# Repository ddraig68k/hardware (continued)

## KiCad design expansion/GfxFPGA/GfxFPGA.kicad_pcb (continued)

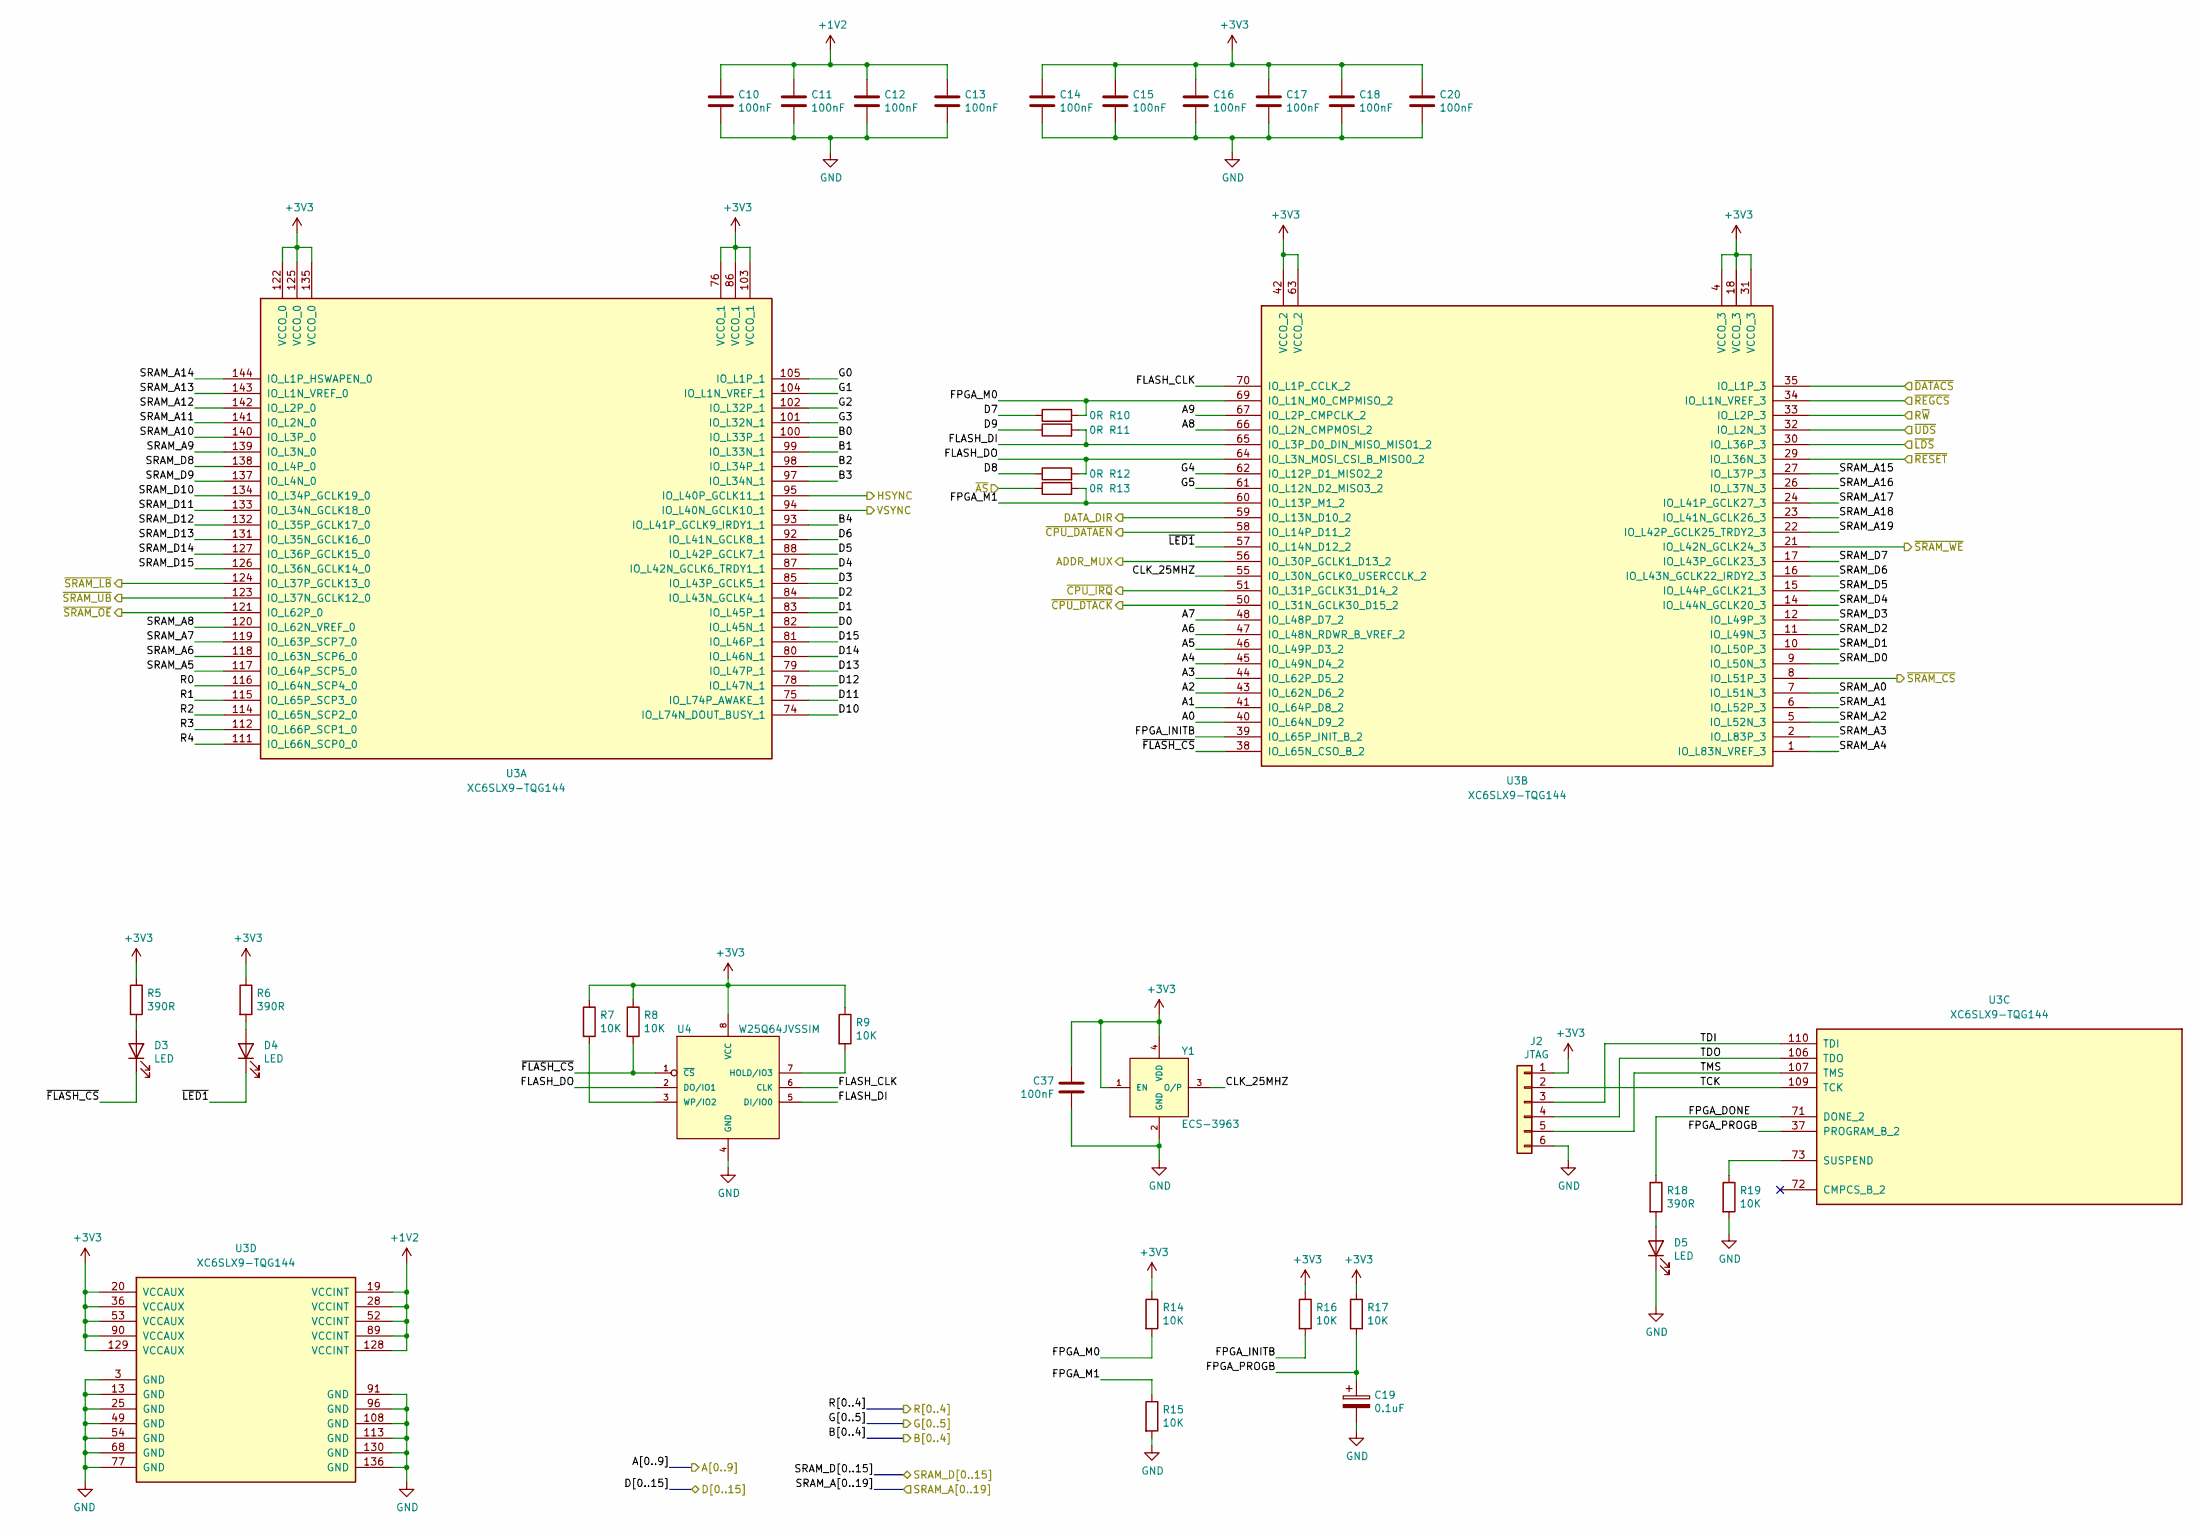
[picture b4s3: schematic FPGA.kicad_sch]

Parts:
C10, C11, C12, C13, C14, C15, C16, C17, C18, C20, C37: 100nF; C_0805_2012Metric
C19: 0.1uF; CP_Elec_4x5.3
D3, D4, D5: LED; LED_1206_3216Metric
J2: JTAG; PinHeader_1x06_P2.54mm_Vertical
R5, R6, R18: 390R; R_0805_2012Metric
R7, R8, R9, R14, R15, R16, R17, R19: 10K; R_0805_2012Metric
R10, R11, R12, R13: 0R; R_0805_2012Metric
U3: XC6SLX9-TQG144; TQ144
U4: W25Q64JVSSIM; SOIC127P790X195-8N
Y1: ECS-3963; OSC_ECS-3963; PARTREV N/A

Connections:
+1V2: C10.1, C11.1, C12.1, C13.1, U3.19 (VCCINT), U3.28 (VCCINT), U3.52 (VCCINT), U3.89 (VCCINT), U3.128 (VCCINT); also elsewhere on the board
+3V3: C14.1, C15.1, C16.1, C17.1, C18.1, C20.1, C37.1, J2.1, R5.1, R6.1, R7.1, R8.1, R9.1, R14.1, R16.1, R17.1, U3.4 (VCCO_3), U3.18 (VCCO_3), U3.20 (VCCAUX), U3.31 (VCCO_3), U3.36 (VCCAUX), U3.42 (VCCO_2), U3.53 (VCCAUX), U3.63 (VCCO_2), U3.76 (VCCO_1), U3.86 (VCCO_1), U3.90 (VCCAUX), U3.103 (VCCO_1), U3.122 (VCCO_0), U3.125 (VCCO_0), U3.129 (VCCAUX), U3.135 (VCCO_0), U4.8 (VCC), Y1.1 (EN), Y1.4 (VDD); also elsewhere on the board
/FPGA/A0: U3.40 (IO_L64N_D9_2); also elsewhere on the board
/FPGA/A1: U3.41 (IO_L64P_D8_2); also elsewhere on the board
/FPGA/A2: U3.43 (IO_L62N_D6_2); also elsewhere on the board
/FPGA/A3: U3.44 (IO_L62P_D5_2); also elsewhere on the board
/FPGA/A4: U3.45 (IO_L49N_D4_2); also elsewhere on the board
/FPGA/A5: U3.46 (IO_L49P_D3_2); also elsewhere on the board
/FPGA/A6: U3.47 (IO_L48N_RDWR_B_VREF_2); also elsewhere on the board
/FPGA/A7: U3.48 (IO_L48P_D7_2); also elsewhere on the board
/FPGA/A8: U3.66 (IO_L2N_CMPMOSI_2); also elsewhere on the board
/FPGA/A9: U3.67 (IO_L2P_CMPCLK_2); also elsewhere on the board
/FPGA/ADDR_MUX: U3.56 (IO_L30P_GCLK1_D13_2); also elsewhere on the board
/FPGA/B0: U3.100 (IO_L33P_1); also elsewhere on the board
/FPGA/B1: U3.99 (IO_L33N_1); also elsewhere on the board
/FPGA/B2: U3.98 (IO_L34P_1); also elsewhere on the board
/FPGA/B3: U3.97 (IO_L34N_1); also elsewhere on the board
/FPGA/B4: U3.93 (IO_L41P_GCLK9_IRDY1_1); also elsewhere on the board
/FPGA/CLK_25MHZ: U3.55 (IO_L30N_GCLK0_USERCCLK_2), Y1.3 (O/P)
/FPGA/D0: U3.82 (IO_L45N_1); also elsewhere on the board
/FPGA/D1: U3.83 (IO_L45P_1); also elsewhere on the board
/FPGA/D2: U3.84 (IO_L43N_GCLK4_1); also elsewhere on the board
/FPGA/D3: U3.85 (IO_L43P_GCLK5_1); also elsewhere on the board
/FPGA/D4: U3.87 (IO_L42N_GCLK6_TRDY1_1); also elsewhere on the board
/FPGA/D5: U3.88 (IO_L42P_GCLK7_1); also elsewhere on the board
/FPGA/D6: U3.92 (IO_L41N_GCLK8_1); also elsewhere on the board
/FPGA/D7: R10.1; also elsewhere on the board
/FPGA/D8: R12.1; also elsewhere on the board
/FPGA/D9: R11.1; also elsewhere on the board
/FPGA/D10: U3.74 (IO_L74N_DOUT_BUSY_1); also elsewhere on the board
/FPGA/D11: U3.75 (IO_L74P_AWAKE_1); also elsewhere on the board
/FPGA/D12: U3.78 (IO_L47N_1); also elsewhere on the board
/FPGA/D13: U3.79 (IO_L47P_1); also elsewhere on the board
/FPGA/D14: U3.80 (IO_L46N_1); also elsewhere on the board
/FPGA/D15: U3.81 (IO_L46P_1); also elsewhere on the board
/FPGA/DATA_DIR: U3.59 (IO_L13N_D10_2); also elsewhere on the board
/FPGA/FLASH_CLK: U3.70 (IO_L1P_CCLK_2), U4.6 (CLK)
/FPGA/FLASH_DI: R11.2, U3.65 (IO_L3P_D0_DIN_MISO_MISO1_2), U4.5 (DI/IO0)
/FPGA/FLASH_DO: R12.2, U3.64 (IO_L3N_MOSI_CSI_B_MISO0_2), U4.2 (DO/IO1)
/FPGA/FPGA_DONE: R18.1, U3.71 (DONE_2)
/FPGA/FPGA_INITB: R16.2, U3.39 (IO_L65P_INIT_B_2)
/FPGA/FPGA_M0: R10.2, R14.2, U3.69 (IO_L1N_M0_CMPMISO_2)
/FPGA/FPGA_M1: R13.2, R15.1, U3.60 (IO_L13P_M1_2)
/FPGA/FPGA_PROGB: C19.1, R17.2, U3.37 (PROGRAM_B_2)
/FPGA/G0: U3.105 (IO_L1P_1); also elsewhere on the board
/FPGA/G1: U3.104 (IO_L1N_VREF_1); also elsewhere on the board
/FPGA/G2: U3.102 (IO_L32P_1); also elsewhere on the board
/FPGA/G3: U3.101 (IO_L32N_1); also elsewhere on the board
/FPGA/G4: U3.62 (IO_L12P_D1_MISO2_2); also elsewhere on the board
/FPGA/G5: U3.61 (IO_L12N_D2_MISO3_2); also elsewhere on the board
/FPGA/HSYNC: U3.95 (IO_L40P_GCLK11_1); also elsewhere on the board
/FPGA/R0: U3.116 (IO_L64N_SCP4_0); also elsewhere on the board
/FPGA/R1: U3.115 (IO_L65P_SCP3_0); also elsewhere on the board
/FPGA/R2: U3.114 (IO_L65N_SCP2_0); also elsewhere on the board
/FPGA/R3: U3.112 (IO_L66P_SCP1_0); also elsewhere on the board
/FPGA/R4: U3.111 (IO_L66N_SCP0_0); also elsewhere on the board
/FPGA/R~W: U3.33 (IO_L2P_3); also elsewhere on the board
/FPGA/SRAM_A0: U3.7 (IO_L51N_3); also elsewhere on the board
/FPGA/SRAM_A1: U3.6 (IO_L52P_3); also elsewhere on the board
/FPGA/SRAM_A2: U3.5 (IO_L52N_3); also elsewhere on the board
/FPGA/SRAM_A3: U3.2 (IO_L83P_3); also elsewhere on the board
/FPGA/SRAM_A4: U3.1 (IO_L83N_VREF_3); also elsewhere on the board
/FPGA/SRAM_A5: U3.117 (IO_L64P_SCP5_0); also elsewhere on the board
/FPGA/SRAM_A6: U3.118 (IO_L63N_SCP6_0); also elsewhere on the board
/FPGA/SRAM_A7: U3.119 (IO_L63P_SCP7_0); also elsewhere on the board
/FPGA/SRAM_A8: U3.120 (IO_L62N_VREF_0); also elsewhere on the board
/FPGA/SRAM_A9: U3.139 (IO_L3N_0); also elsewhere on the board
/FPGA/SRAM_A10: U3.140 (IO_L3P_0); also elsewhere on the board
/FPGA/SRAM_A11: U3.141 (IO_L2N_0); also elsewhere on the board
/FPGA/SRAM_A12: U3.142 (IO_L2P_0); also elsewhere on the board
/FPGA/SRAM_A13: U3.143 (IO_L1N_VREF_0); also elsewhere on the board
/FPGA/SRAM_A14: U3.144 (IO_L1P_HSWAPEN_0); also elsewhere on the board
/FPGA/SRAM_A15: U3.27 (IO_L37P_3); also elsewhere on the board
/FPGA/SRAM_A16: U3.26 (IO_L37N_3); also elsewhere on the board
/FPGA/SRAM_A17: U3.24 (IO_L41P_GCLK27_3); also elsewhere on the board
/FPGA/SRAM_A18: U3.23 (IO_L41N_GCLK26_3); also elsewhere on the board
/FPGA/SRAM_A19: U3.22 (IO_L42P_GCLK25_TRDY2_3); also elsewhere on the board
/FPGA/SRAM_D0: U3.9 (IO_L50N_3); also elsewhere on the board
/FPGA/SRAM_D1: U3.10 (IO_L50P_3); also elsewhere on the board
/FPGA/SRAM_D2: U3.11 (IO_L49N_3); also elsewhere on the board
/FPGA/SRAM_D3: U3.12 (IO_L49P_3); also elsewhere on the board
/FPGA/SRAM_D4: U3.14 (IO_L44N_GCLK20_3); also elsewhere on the board
/FPGA/SRAM_D5: U3.15 (IO_L44P_GCLK21_3); also elsewhere on the board
/FPGA/SRAM_D6: U3.16 (IO_L43N_GCLK22_IRDY2_3); also elsewhere on the board
/FPGA/SRAM_D7: U3.17 (IO_L43P_GCLK23_3); also elsewhere on the board
/FPGA/SRAM_D8: U3.138 (IO_L4P_0); also elsewhere on the board
/FPGA/SRAM_D9: U3.137 (IO_L4N_0); also elsewhere on the board
/FPGA/SRAM_D10: U3.134 (IO_L34P_GCLK19_0); also elsewhere on the board
/FPGA/SRAM_D11: U3.133 (IO_L34N_GCLK18_0); also elsewhere on the board
/FPGA/SRAM_D12: U3.132 (IO_L35P_GCLK17_0); also elsewhere on the board
/FPGA/SRAM_D13: U3.131 (IO_L35N_GCLK16_0); also elsewhere on the board
/FPGA/SRAM_D14: U3.127 (IO_L36P_GCLK15_0); also elsewhere on the board
/FPGA/SRAM_D15: U3.126 (IO_L36N_GCLK14_0); also elsewhere on the board
/FPGA/TCK: J2.2, U3.109 (TCK)
/FPGA/TDI: J2.3, U3.110 (TDI)
/FPGA/TDO: J2.4, U3.106 (TDO)
/FPGA/TMS: J2.5, U3.107 (TMS)
/FPGA/VSYNC: U3.94 (IO_L40N_GCLK10_1); also elsewhere on the board
/FPGA/~AS: R13.1; also elsewhere on the board
/FPGA/~CPU_DATAEN: U3.58 (IO_L14P_D11_2); also elsewhere on the board
/FPGA/~DATACS: U3.35 (IO_L1P_3); also elsewhere on the board
/FPGA/~FLASH_CS: D3.1 (K), R8.2, U3.38 (IO_L65N_CSO_B_2), U4.1 (~CS)
/FPGA/~LDS: U3.30 (IO_L36P_3); also elsewhere on the board
/FPGA/~LED1: D4.1 (K), U3.57 (IO_L14N_D12_2)
/FPGA/~REGCS: U3.34 (IO_L1N_VREF_3); also elsewhere on the board
/FPGA/~RESET: U3.29 (IO_L36N_3); also elsewhere on the board
/FPGA/~SRAM_CS: U3.8 (IO_L51P_3); also elsewhere on the board
/FPGA/~SRAM_LB: U3.124 (IO_L37P_GCLK13_0); also elsewhere on the board
/FPGA/~SRAM_OE: U3.121 (IO_L62P_0); also elsewhere on the board
/FPGA/~SRAM_UB: U3.123 (IO_L37N_GCLK12_0); also elsewhere on the board
/FPGA/~SRAM_WE: U3.21 (IO_L42N_GCLK24_3); also elsewhere on the board
/FPGA/~UDS: U3.32 (IO_L2N_3); also elsewhere on the board
/~CPU_DTACK: U3.50 (IO_L31N_GCLK30_D15_2); also elsewhere on the board
/~CPU_IRQ: U3.51 (IO_L31P_GCLK31_D14_2); also elsewhere on the board
GND: C10.2, C11.2, C12.2, C13.2, C14.2, C15.2, C16.2, C17.2, C18.2, C19.2, C20.2, C37.2, D5.1 (K), J2.6, R15.2, R19.2, U3.3 (GND), U3.13 (GND), U3.25 (GND), U3.49 (GND), U3.54 (GND), U3.68 (GND), U3.77 (GND), U3.91 (GND), U3.96 (GND), U3.108 (GND), U3.113 (GND), U3.130 (GND), U3.136 (GND), U4.4 (GND), Y1.2 (GND); also elsewhere on the board
unnamed: D3.2 (A), R5.2
unnamed: D4.2 (A), R6.2
unnamed: D5.2 (A), R18.2
unnamed: R19.1, U3.73 (SUSPEND)
unnamed: R9.2, U4.7 (HOLD/IO3)
unnamed: R7.2, U4.3 (WP/IO2)

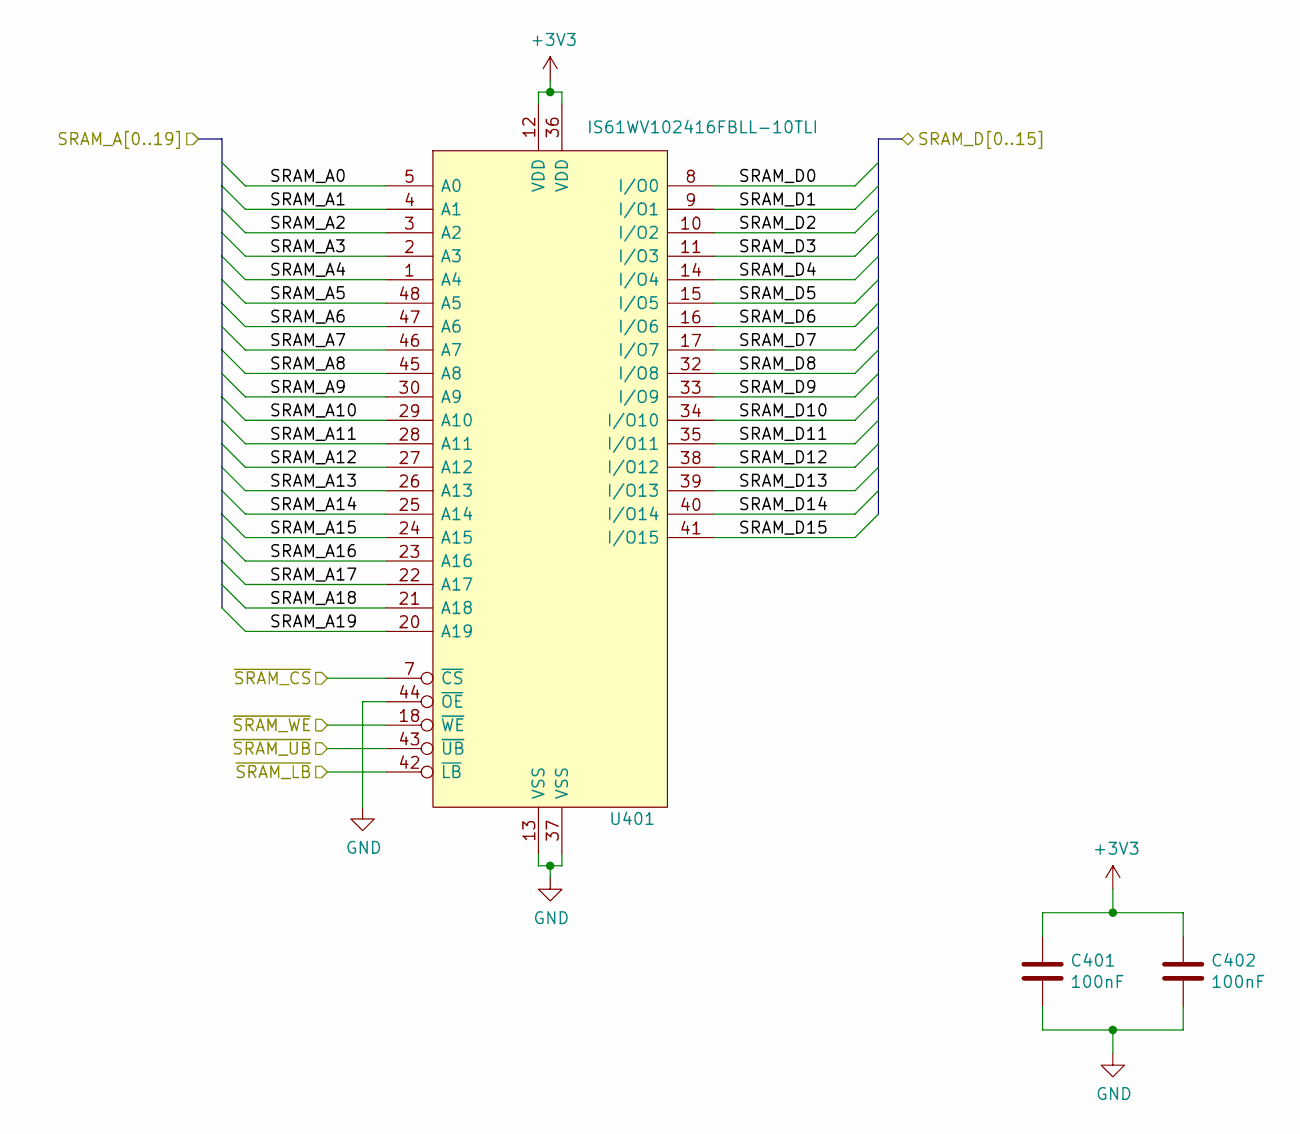
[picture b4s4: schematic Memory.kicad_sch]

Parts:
C401, C402: 100nF; C_0805_2012Metric
U401: IS61WV102416FBLL-10TLI; SOP50P2000X120-48N; Manufacturer_Part_Number IS61WV102416FBLL-10TLI; Mouser Part Number 870-61WV12416FBL1TLI

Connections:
unnamed: C401.1, C402.1, U401.12 (VDD), U401.36 (VDD)
unnamed: C401.2, C402.2, U401.13 (VSS), U401.37 (VSS), U401.44 (~OE)

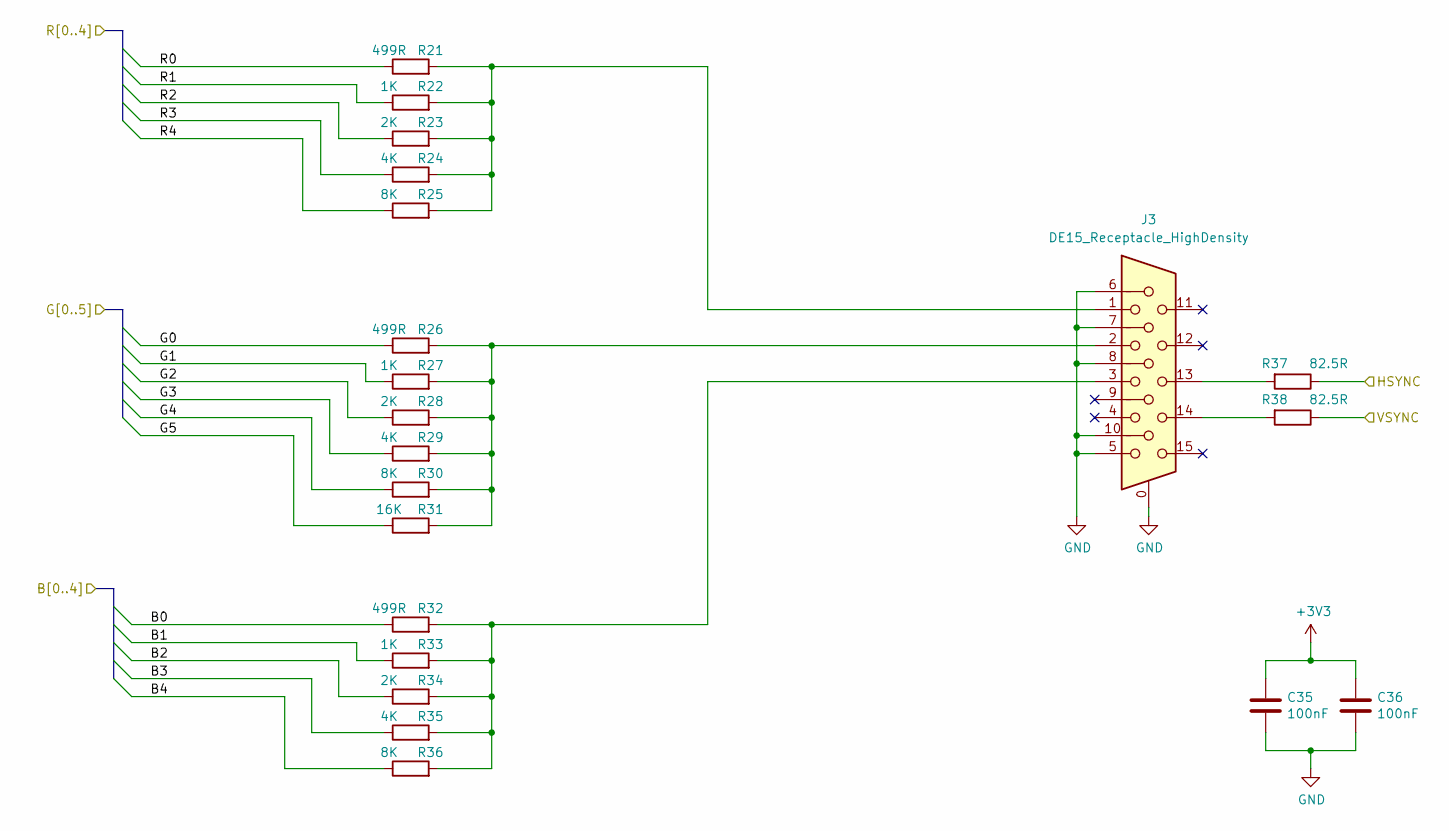
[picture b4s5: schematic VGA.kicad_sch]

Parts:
C35, C36: 100nF; C_0805_2012Metric
J3: DE15_Receptacle_HighDensity; DSUB-15-HD_Female_Horizontal_P2.29x1.98mm_EdgePinOffset3.03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
R21, R26, R32: 499R; R_0805_2012Metric
R22, R27, R33: 1K; R_0805_2012Metric
R23, R28, R34: 2K; R_0805_2012Metric
R24, R29, R35: 4K; R_0805_2012Metric
R25, R30, R36: 8K; R_0805_2012Metric
R31: 16K; R_0805_2012Metric
R37, R38: 82.5R; R_0805_2012Metric

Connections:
+3V3: C35.1, C36.1; also elsewhere on the board
/FPGA/B0: R32.1; also elsewhere on the board
/FPGA/B1: R33.1; also elsewhere on the board
/FPGA/B2: R34.1; also elsewhere on the board
/FPGA/B3: R35.1; also elsewhere on the board
/FPGA/B4: R36.1; also elsewhere on the board
/FPGA/G0: R26.1; also elsewhere on the board
/FPGA/G1: R27.1; also elsewhere on the board
/FPGA/G2: R28.1; also elsewhere on the board
/FPGA/G3: R29.1; also elsewhere on the board
/FPGA/G4: R30.1; also elsewhere on the board
/FPGA/G5: R31.1; also elsewhere on the board
/FPGA/HSYNC: R37.1; also elsewhere on the board
/FPGA/R0: R21.1; also elsewhere on the board
/FPGA/R1: R22.1; also elsewhere on the board
/FPGA/R2: R23.1; also elsewhere on the board
/FPGA/R3: R24.1; also elsewhere on the board
/FPGA/R4: R25.1; also elsewhere on the board
/FPGA/VSYNC: R38.1; also elsewhere on the board
GND: C35.2, C36.2, J3.0, J3.5, J3.6, J3.7, J3.8, J3.10; also elsewhere on the board
unnamed: J3.1, R21.2, R22.2, R23.2, R24.2, R25.2
unnamed: J3.2, R26.2, R27.2, R28.2, R29.2, R30.2, R31.2
unnamed: J3.3, R32.2, R33.2, R34.2, R35.2, R36.2
unnamed: J3.13, R37.2
unnamed: J3.14, R38.2

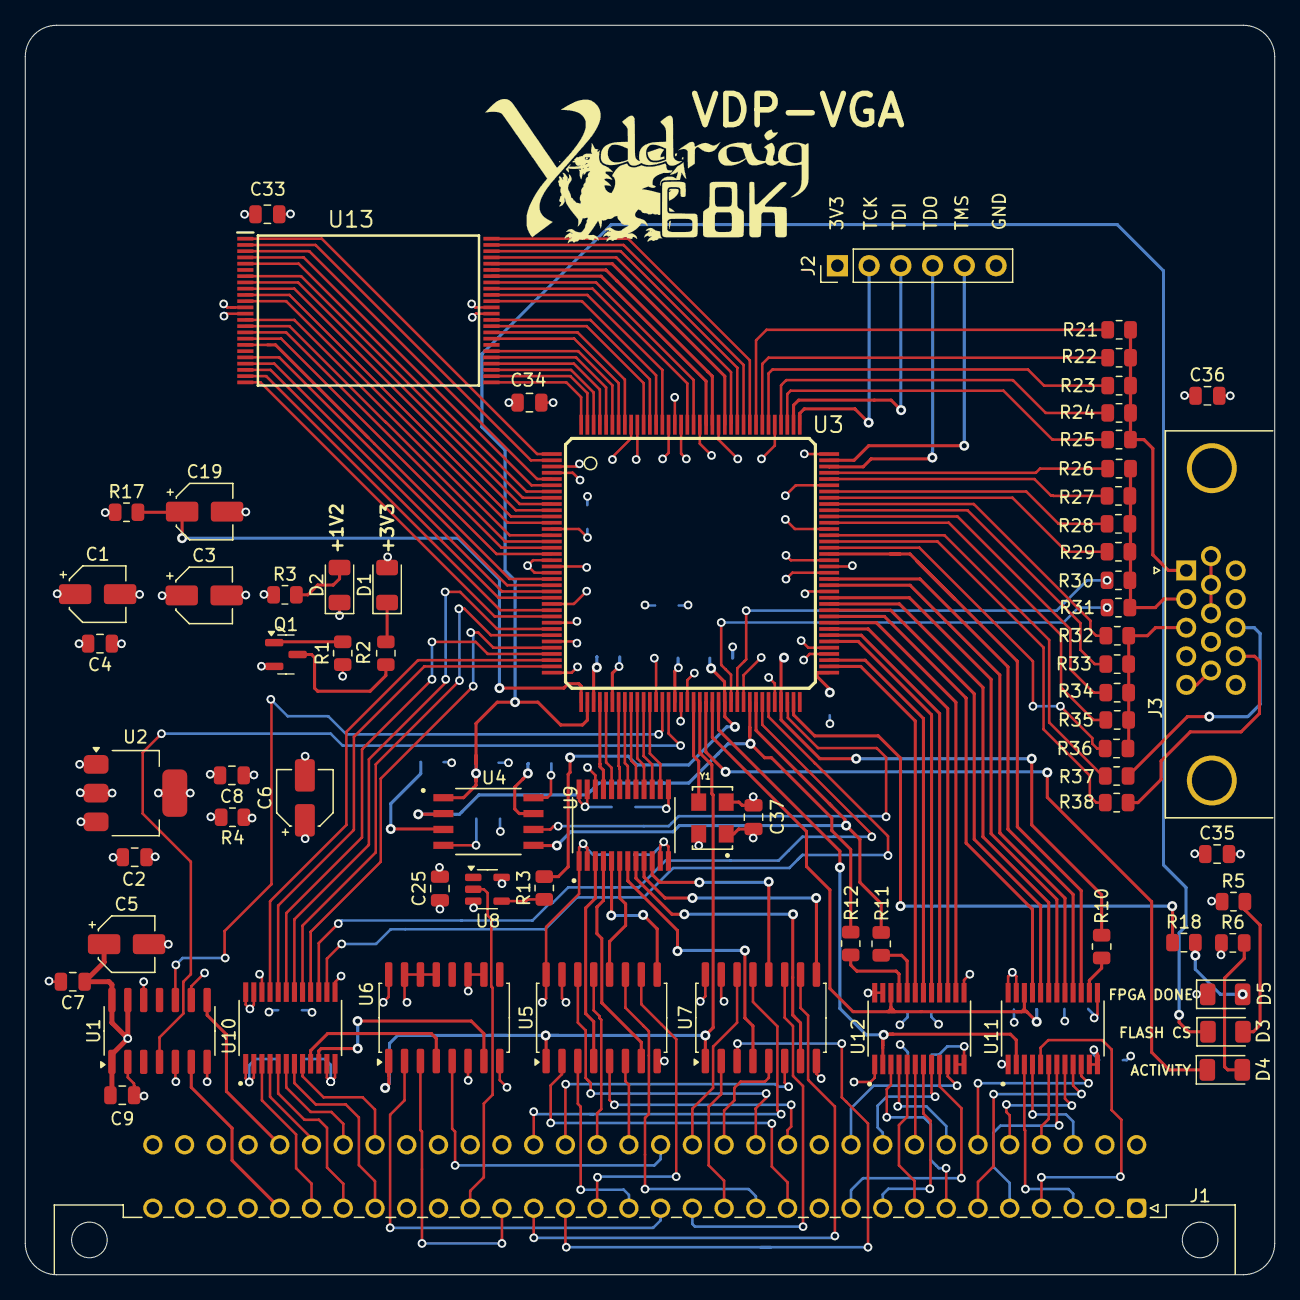
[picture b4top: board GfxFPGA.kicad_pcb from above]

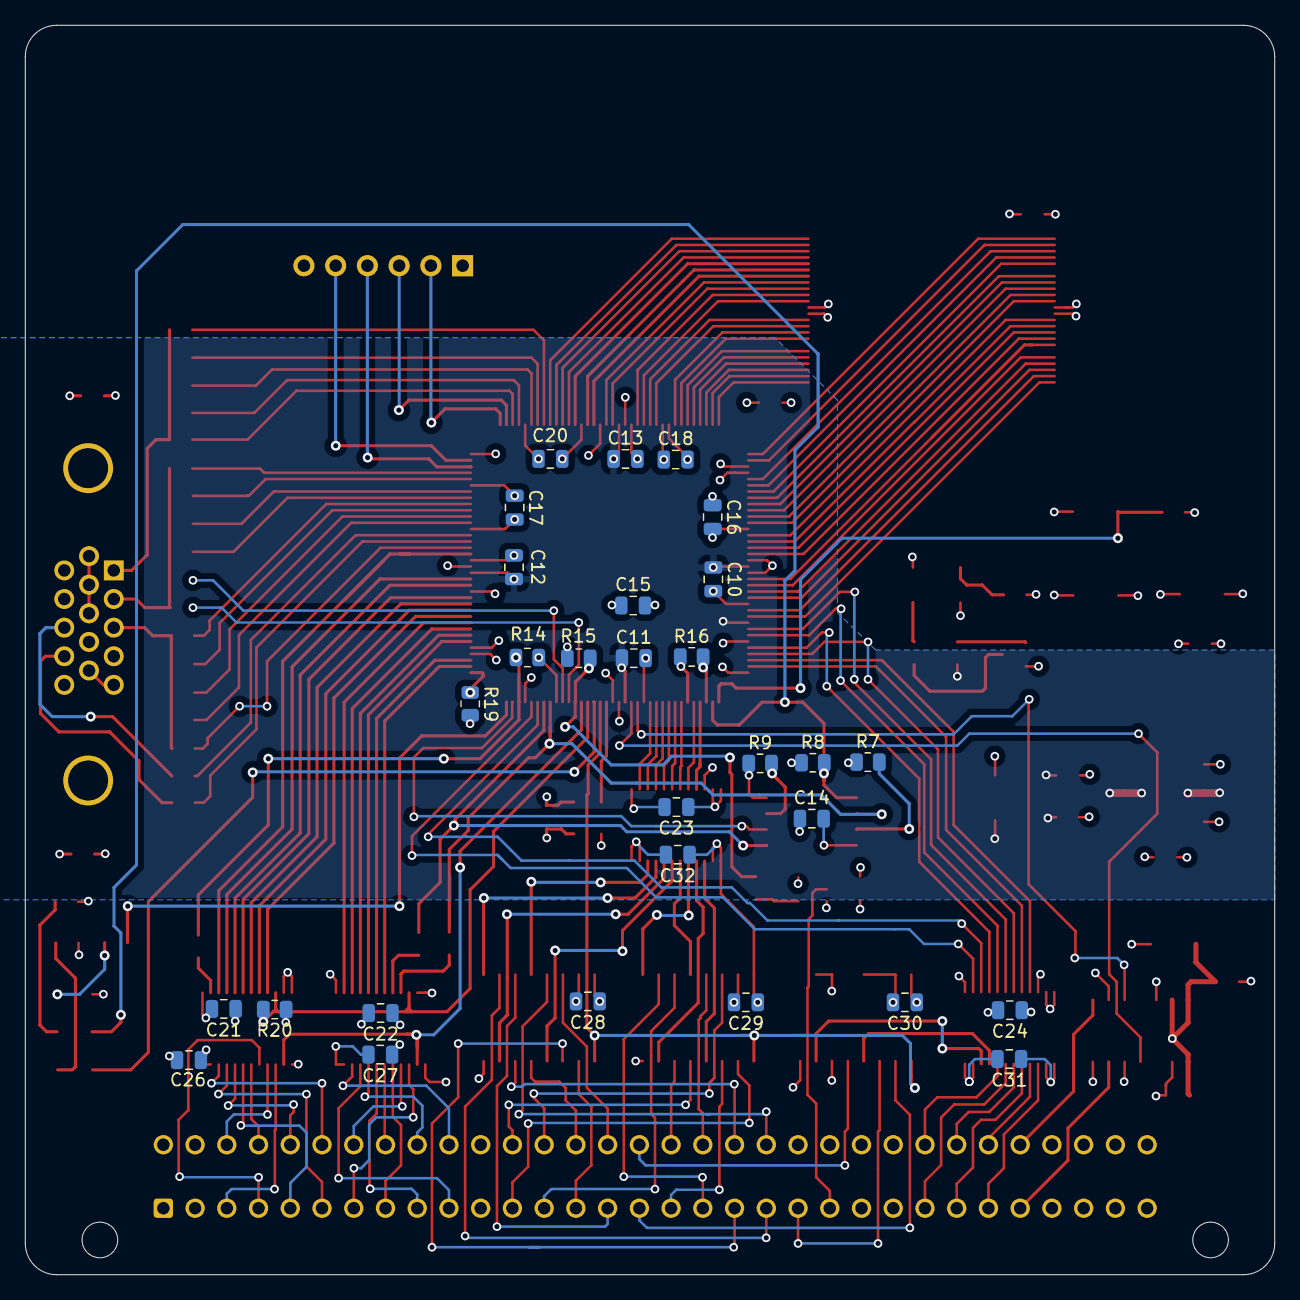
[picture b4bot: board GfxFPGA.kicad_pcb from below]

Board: 4 copper layers, 100.0 x 100.0 mm, 99 parts (29 on the bottom side), 185 nets.

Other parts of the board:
C33, C34: 100nF; C_0805_2012Metric
U13: IS61WV102416FBLL-10TLI; SOP50P2000X120-48N

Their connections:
+3V3: C33.1, C34.1, U13.12 (VDD), U13.36 (VDD); also elsewhere on the board
/FPGA/SRAM_A0: U13.5 (A0); also elsewhere on the board
/FPGA/SRAM_A1: U13.4 (A1); also elsewhere on the board
/FPGA/SRAM_A2: U13.3 (A2); also elsewhere on the board
/FPGA/SRAM_A3: U13.2 (A3); also elsewhere on the board
/FPGA/SRAM_A4: U13.1 (A4); also elsewhere on the board
/FPGA/SRAM_A5: U13.48 (A5); also elsewhere on the board
/FPGA/SRAM_A6: U13.47 (A6); also elsewhere on the board
/FPGA/SRAM_A7: U13.46 (A7); also elsewhere on the board
/FPGA/SRAM_A8: U13.45 (A8); also elsewhere on the board
/FPGA/SRAM_A9: U13.30 (A9); also elsewhere on the board
/FPGA/SRAM_A10: U13.29 (A10); also elsewhere on the board
/FPGA/SRAM_A11: U13.28 (A11); also elsewhere on the board
/FPGA/SRAM_A12: U13.27 (A12); also elsewhere on the board
/FPGA/SRAM_A13: U13.26 (A13); also elsewhere on the board
/FPGA/SRAM_A14: U13.25 (A14); also elsewhere on the board
/FPGA/SRAM_A15: U13.24 (A15); also elsewhere on the board
/FPGA/SRAM_A16: U13.23 (A16); also elsewhere on the board
/FPGA/SRAM_A17: U13.22 (A17); also elsewhere on the board
/FPGA/SRAM_A18: U13.21 (A18); also elsewhere on the board
/FPGA/SRAM_A19: U13.20 (A19); also elsewhere on the board
/FPGA/SRAM_D0: U13.8 (I/O0); also elsewhere on the board
/FPGA/SRAM_D1: U13.9 (I/O1); also elsewhere on the board
/FPGA/SRAM_D2: U13.10 (I/O2); also elsewhere on the board
/FPGA/SRAM_D3: U13.11 (I/O3); also elsewhere on the board
/FPGA/SRAM_D4: U13.14 (I/O4); also elsewhere on the board
/FPGA/SRAM_D5: U13.15 (I/O5); also elsewhere on the board
/FPGA/SRAM_D6: U13.16 (I/O6); also elsewhere on the board
/FPGA/SRAM_D7: U13.17 (I/O7); also elsewhere on the board
/FPGA/SRAM_D8: U13.32 (I/O8); also elsewhere on the board
/FPGA/SRAM_D9: U13.33 (I/O9); also elsewhere on the board
/FPGA/SRAM_D10: U13.34 (I/O10); also elsewhere on the board
/FPGA/SRAM_D11: U13.35 (I/O11); also elsewhere on the board
/FPGA/SRAM_D12: U13.38 (I/O12); also elsewhere on the board
/FPGA/SRAM_D13: U13.39 (I/O13); also elsewhere on the board
/FPGA/SRAM_D14: U13.40 (I/O14); also elsewhere on the board
/FPGA/SRAM_D15: U13.41 (I/O15); also elsewhere on the board
/FPGA/~SRAM_CS: U13.7 (~CS); also elsewhere on the board
/FPGA/~SRAM_LB: U13.42 (~LB); also elsewhere on the board
/FPGA/~SRAM_OE: U13.44 (~OE); also elsewhere on the board
/FPGA/~SRAM_UB: U13.43 (~UB); also elsewhere on the board
/FPGA/~SRAM_WE: U13.18 (~WE); also elsewhere on the board
GND: C33.2, C34.2, U13.13 (VSS), U13.37 (VSS); also elsewhere on the board

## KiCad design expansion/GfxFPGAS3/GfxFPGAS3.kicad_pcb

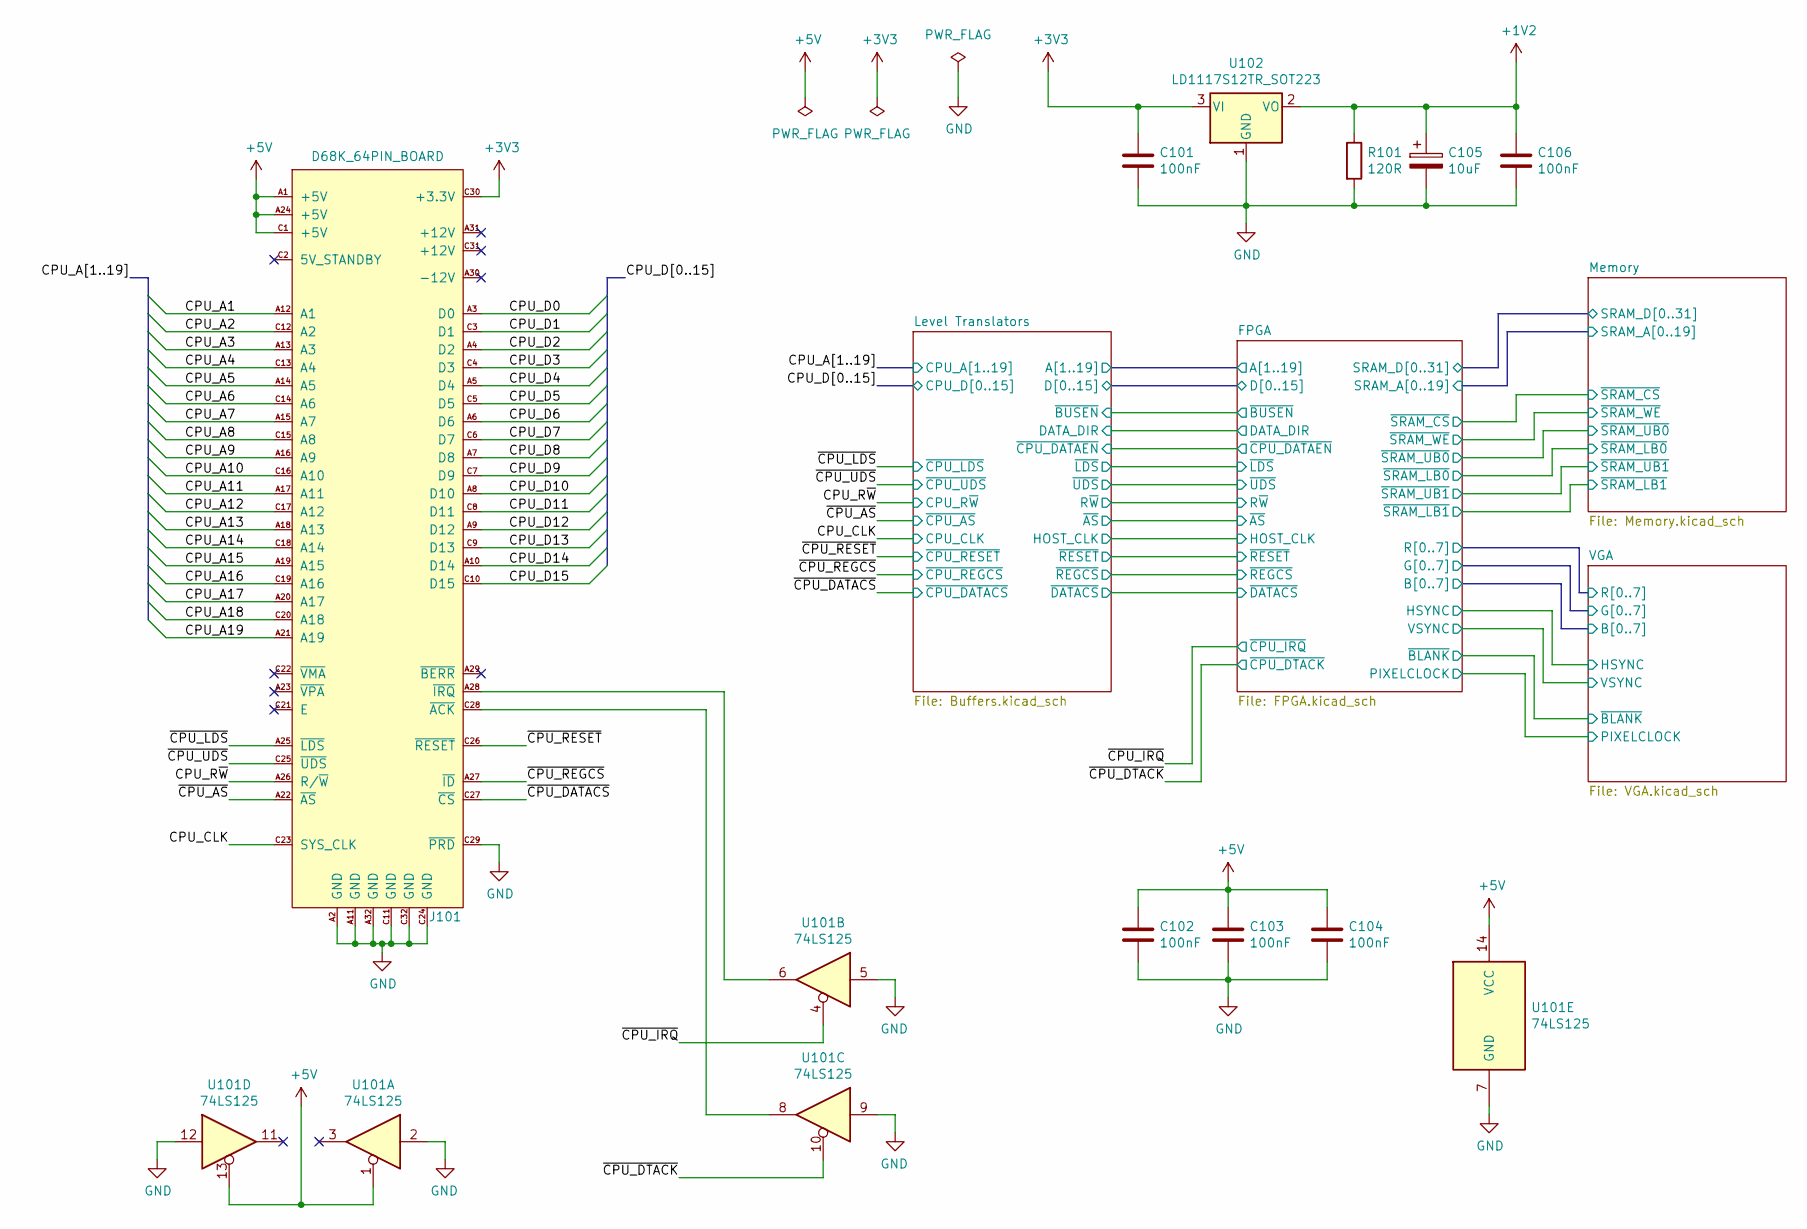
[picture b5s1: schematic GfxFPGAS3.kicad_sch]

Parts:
C101, C102, C103, C104, C106: 100nF; C_0805_2012Metric
C105: 10uF; CP_Elec_4x5.3
J101: D68K_64PIN_BOARD; DIN41612_C_2x32_Male_Horizontal_THT
R101: 120R; R_0805_2012Metric
U101: 74LS125; SO-14_3.9x8.65mm_P1.27mm
U102: LD1117S12TR_SOT223; SOT-223-3_TabPin2

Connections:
+1V2: C105.1, C106.1, R101.1, U102.2 (VO); also elsewhere on the board
+5V: C102.1, C103.1, C104.1, J101.A1 (+5V), J101.A24 (+5V), J101.C1 (+5V), U101.1, U101.13, U101.14 (VCC); also elsewhere on the board
/CPU_A1: J101.A12 (A1); also elsewhere on the board
/CPU_A2: J101.C12 (A2); also elsewhere on the board
/CPU_A3: J101.A13 (A3); also elsewhere on the board
/CPU_A4: J101.C13 (A4); also elsewhere on the board
/CPU_A5: J101.A14 (A5); also elsewhere on the board
/CPU_A6: J101.C14 (A6); also elsewhere on the board
/CPU_A7: J101.A15 (A7); also elsewhere on the board
/CPU_A8: J101.C15 (A8); also elsewhere on the board
/CPU_A9: J101.A16 (A9); also elsewhere on the board
/CPU_A10: J101.C16 (A10); also elsewhere on the board
/CPU_A11: J101.A17 (A11); also elsewhere on the board
/CPU_A12: J101.C17 (A12); also elsewhere on the board
/CPU_A13: J101.A18 (A13); also elsewhere on the board
/CPU_A14: J101.C18 (A14); also elsewhere on the board
/CPU_A15: J101.A19 (A15); also elsewhere on the board
/CPU_A16: J101.C19 (A16); also elsewhere on the board
/CPU_A17: J101.A20 (A17); also elsewhere on the board
/CPU_A18: J101.C20 (A18); also elsewhere on the board
/CPU_A19: J101.A21 (A19); also elsewhere on the board
/CPU_CLK: J101.C23 (SYS_CLK); also elsewhere on the board
/CPU_D0: J101.A3 (D0); also elsewhere on the board
/CPU_D1: J101.C3 (D1); also elsewhere on the board
/CPU_D2: J101.A4 (D2); also elsewhere on the board
/CPU_D3: J101.C4 (D3); also elsewhere on the board
/CPU_D4: J101.A5 (D4); also elsewhere on the board
/CPU_D5: J101.C5 (D5); also elsewhere on the board
/CPU_D6: J101.A6 (D6); also elsewhere on the board
/CPU_D7: J101.C6 (D7); also elsewhere on the board
/CPU_D8: J101.A7 (D8); also elsewhere on the board
/CPU_D9: J101.C7 (D9); also elsewhere on the board
/CPU_D10: J101.A8 (D10); also elsewhere on the board
/CPU_D11: J101.C8 (D11); also elsewhere on the board
/CPU_D12: J101.A9 (D12); also elsewhere on the board
/CPU_D13: J101.C9 (D13); also elsewhere on the board
/CPU_D14: J101.A10 (D14); also elsewhere on the board
/CPU_D15: J101.C10 (D15); also elsewhere on the board
/CPU_R~W: J101.A26 (R/~W); also elsewhere on the board
/~CPU_AS: J101.A22 (~AS); also elsewhere on the board
/~CPU_DATACS: J101.C27 (~CS); also elsewhere on the board
/~CPU_DTACK: U101.10; also elsewhere on the board
/~CPU_IRQ: U101.4; also elsewhere on the board
/~CPU_LDS: J101.A25 (~LDS); also elsewhere on the board
/~CPU_REGCS: J101.A27 (~ID); also elsewhere on the board
/~CPU_RESET: J101.C26 (~RESET); also elsewhere on the board
/~CPU_UDS: J101.C25 (~UDS); also elsewhere on the board
GND: C101.2, C102.2, C103.2, C104.2, C105.2, C106.2, J101.A2 (GND), J101.A11 (GND), J101.A32 (GND), J101.C11 (GND), J101.C24 (GND), J101.C29 (~PRD), J101.C32 (GND), R101.2, U101.2, U101.5, U101.7 (GND), U101.9, U101.12, U102.1 (GND); also elsewhere on the board
unnamed: J101.A28 (~IRQ), U101.6
unnamed: J101.C28 (~ACK), U101.8
